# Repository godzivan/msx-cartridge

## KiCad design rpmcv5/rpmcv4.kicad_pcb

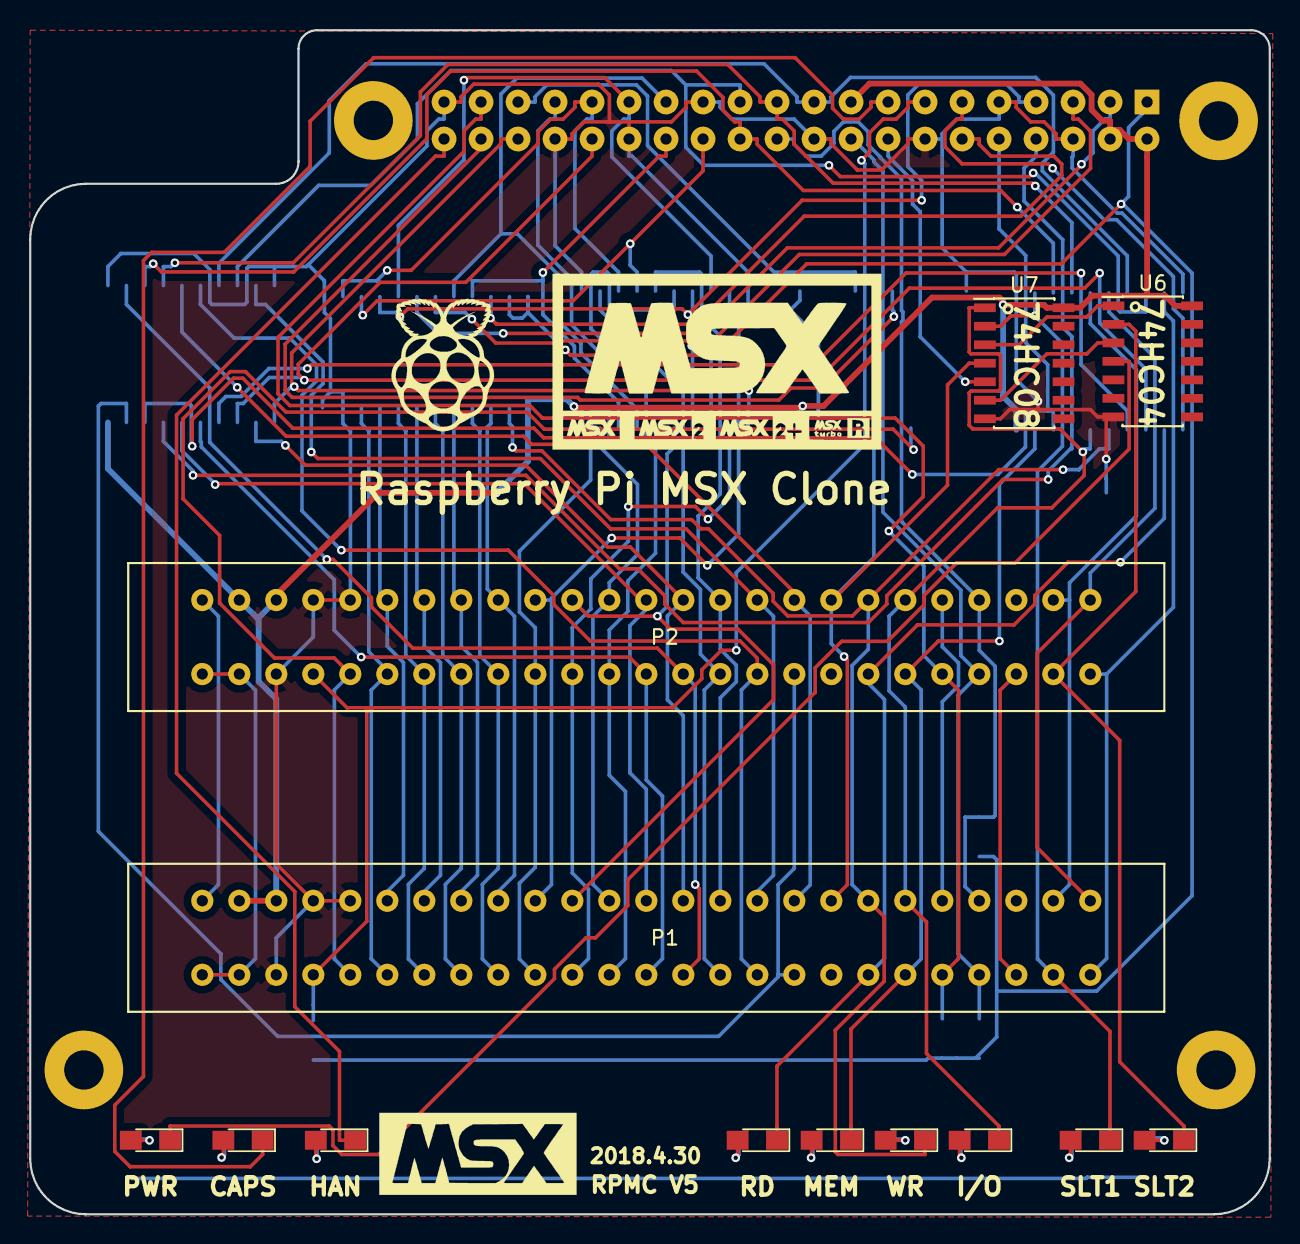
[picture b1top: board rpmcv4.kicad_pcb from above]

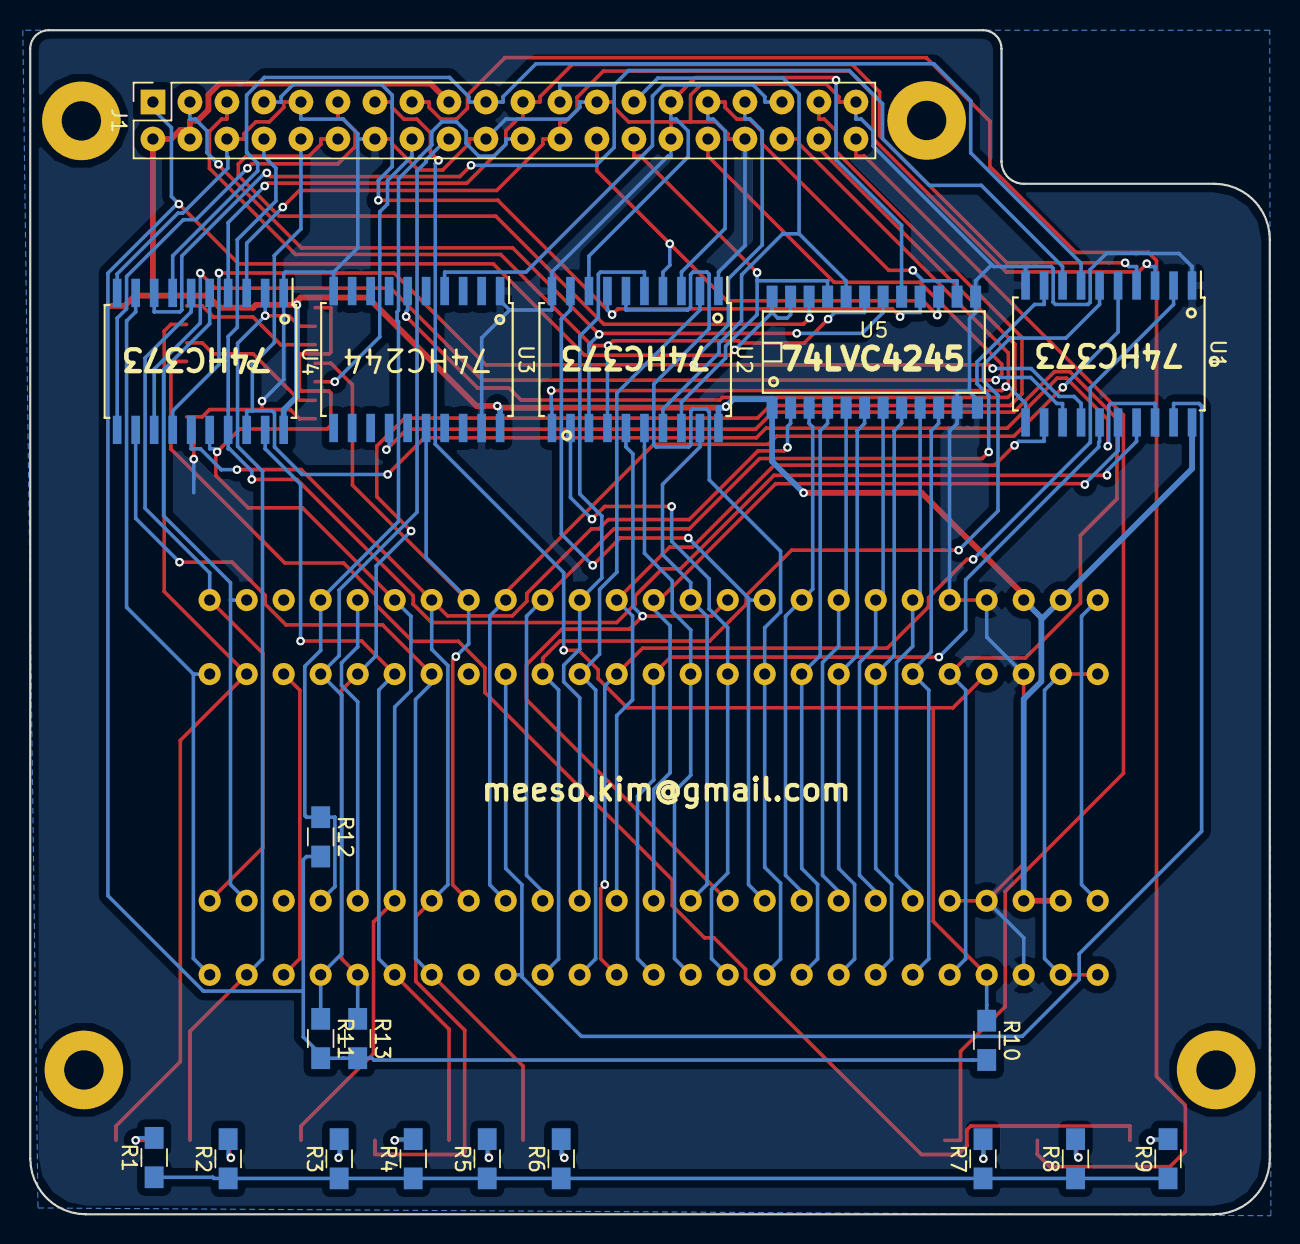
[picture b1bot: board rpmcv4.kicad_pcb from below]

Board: 2 copper layers, 85.1 x 81.3 mm, 38 parts (19 on the bottom side), 83 nets.

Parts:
D1, D2, D3, D4, D5, D6, D7, D8, D9: Led_Small; LED_0805_HandSoldering
G1: LOGO; raspberry_pi_logo
G2: LOGO; msx_msx2_msx+logo
J1: RPi_GPIO; Socket_Strip_Straight_2x20_Pitch2.54mm
P1, P2: CONN_02X25; MSX_SLOT
R1, R2, R3, R4, R5, R6, R7, R8, R9, R10, R11, R12, R13: R; R_0805_HandSoldering
REF1, REF2, REF3, REF4: MountingHole_2.7mm_Pad
U1, U2, U4: 74LS373; SOIC-20W_7.5x12.8mm_Pitch1.27mm
U3: 74HC244; SOIC-20W_7.5x12.8mm_Pitch1.27mm
U5: LVC4245; SOIC-24
U6: 74HC04; SOIC-14_3.9x8.7mm_Pitch1.27mm
U7: 74LS08; SOIC-14_3.9x8.7mm_Pitch1.27mm

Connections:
+3V3: J1.1, R10.2, R11.2, R12.2, R13.2, U5.23, U5.24
+5V: J1.2, J1.4, J1.17, P1.45, P1.47, P2.45, P2.47, U1.20, U2.20, U3.20, U4.20, U5.1, U6.14, U7.14
/+12V: P1.48, P1.50, P2.48, P2.50
/A0: P1.28, P2.28, U2.16
/A1: P1.27, P2.27, U2.19
/A2: P1.30, P2.30, U2.12
/A3: P1.29, P2.29, U2.15
/A4: P1.32, P2.32, U2.6
/A5: P1.31, P2.31, U2.9
/A6: P1.22, P2.22, U2.2
/A7: P1.21, P2.21, U2.5
/A8: P1.24, P2.24, U1.2
/A9: P1.17, P2.17, U1.5
/A10: P1.20, P2.20, U1.6
/A11: P1.19, P2.19, U1.9
/A12: P1.23, P2.23, U1.12
/A13: P1.26, P2.26, U1.15
/A14: P1.25, P2.25, U1.16
/A15: P1.18, P2.18, U1.19
/BUSDIR: J1.37, P1.10, P2.10, R13.1
/CAPS: D8.1, J1.15
/CLK: P1.42, P2.42, U3.14
/CS1: P1.1, P2.1, U4.6
/CS2: P1.2, P2.2, U4.9
/CS12: P1.3, P2.3, U4.5
/D0: P1.34, P2.34, U5.4
/D1: P1.33, P2.33, U5.3
/D2: P1.36, P2.36, U5.6
/D3: P1.35, P2.35, U5.5
/D4: P1.38, P2.38, U5.8
/D5: P1.37, P2.37, U5.7
/D6: P1.40, P2.40, U5.10
/D7: P1.39, P2.39, U5.9
/HAN: D7.1, J1.40
/INT: J1.18, P1.8, P2.8, R11.1
/IORQ: D3.1, P1.11, P2.11, U4.16, U7.1
/M1: P1.9, P2.9
/MREQ: D5.1, P1.12, P2.12, U4.19
/PWR: D9.1, U6.4
/RA8: J1.24, U1.3, U4.3
/RA9: J1.21, U1.4, U4.4
/RA10: J1.19, U1.7, U4.7
/RA11: J1.23, U1.8, U4.8
/RA12: J1.32, U1.13, U4.13
/RA13: J1.33, U1.14, U4.14
/RA14: J1.8, U1.17, U4.17
/RA15: J1.10, U1.18, U4.18
/RC16: J1.36, U1.11, U2.11
/RC17: J1.11, U4.11
/RC18: J1.12, U5.22
/RC19: J1.35, U3.4
/RC20: J1.38, U3.6
/RC23: J1.16, U7.5
/RC25: J1.22, P1.7, P2.7, R12.1
/RC27: J1.13, P1.44, P2.44, R10.1
/RD: D6.1, P1.14, P2.14, U4.12
/RD0: J1.27, U2.17, U5.20
/RD1: J1.28, U2.18, U5.21
/RD2: J1.3, U2.13, U5.18
/RD3: J1.5, U2.14, U5.19
/RD4: J1.7, U2.7, U5.16
/RD5: J1.29, U2.8, U5.17
/RD6: J1.31, U2.3, U5.14
/RD7: J1.26, U2.4, U5.15
/RESET: P1.15, P2.15, U3.16, U7.4
/RFSH: P1.6, P2.6
/SLTSL1: D2.1, P1.4, U4.2, U7.2
/SLTSL3: D1.1, P2.4, U6.2
/SNDIN: P1.49, P2.49
/V3.3: R1.1, R2.1, R3.1, R4.1, R5.1, R6.1, R7.1, R8.1, R9.1
/WR: D4.1, P1.13, P2.13, U4.15, U5.2
/nPWR: U6.3, U7.6
/nSLTSL3: U6.1, U7.3
GND: J1.6, J1.9, J1.14, J1.20, J1.25, J1.30, J1.34, J1.39, P1.41, P1.43, P1.46, P2.41, P2.43, P2.46, U1.1, U1.10, U2.1, U2.10, U3.1, U3.10, U3.19, U4.1, U4.10, U5.11, U5.12, U5.13, U6.7, U7.7
unnamed: D1.2, R1.2
unnamed: D2.2, R2.2
unnamed: D3.2, R3.2
unnamed: D4.2, R4.2
unnamed: D5.2, R5.2
unnamed: D6.2, R6.2
unnamed: D7.2, R7.2
unnamed: D8.2, R8.2
unnamed: D9.2, R9.2

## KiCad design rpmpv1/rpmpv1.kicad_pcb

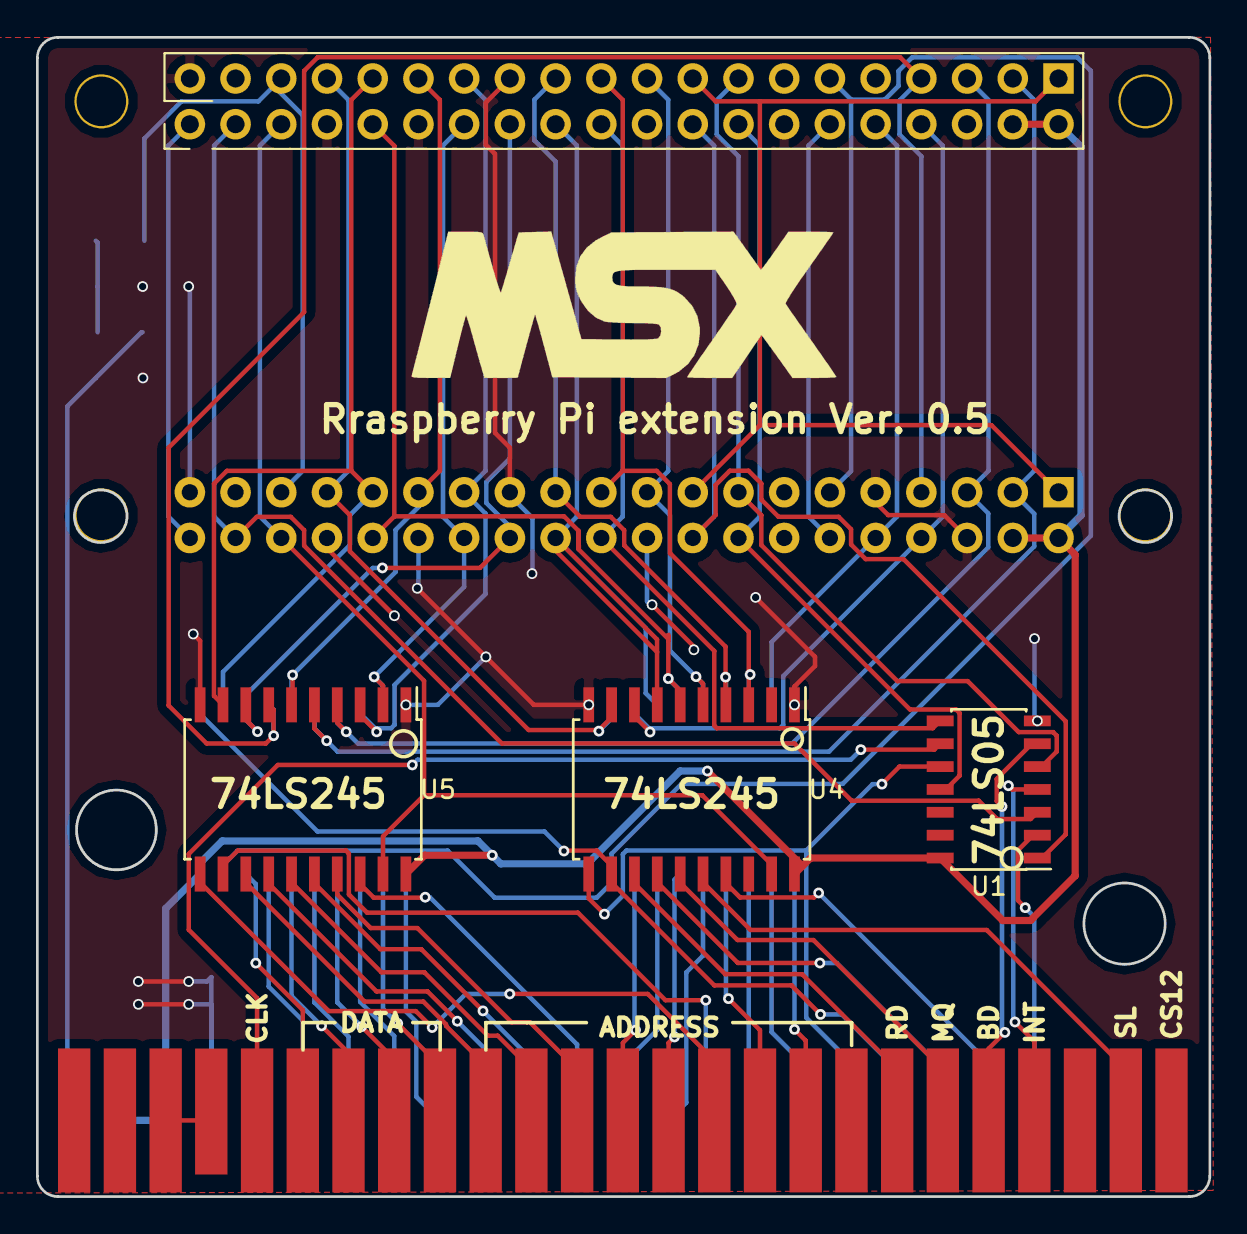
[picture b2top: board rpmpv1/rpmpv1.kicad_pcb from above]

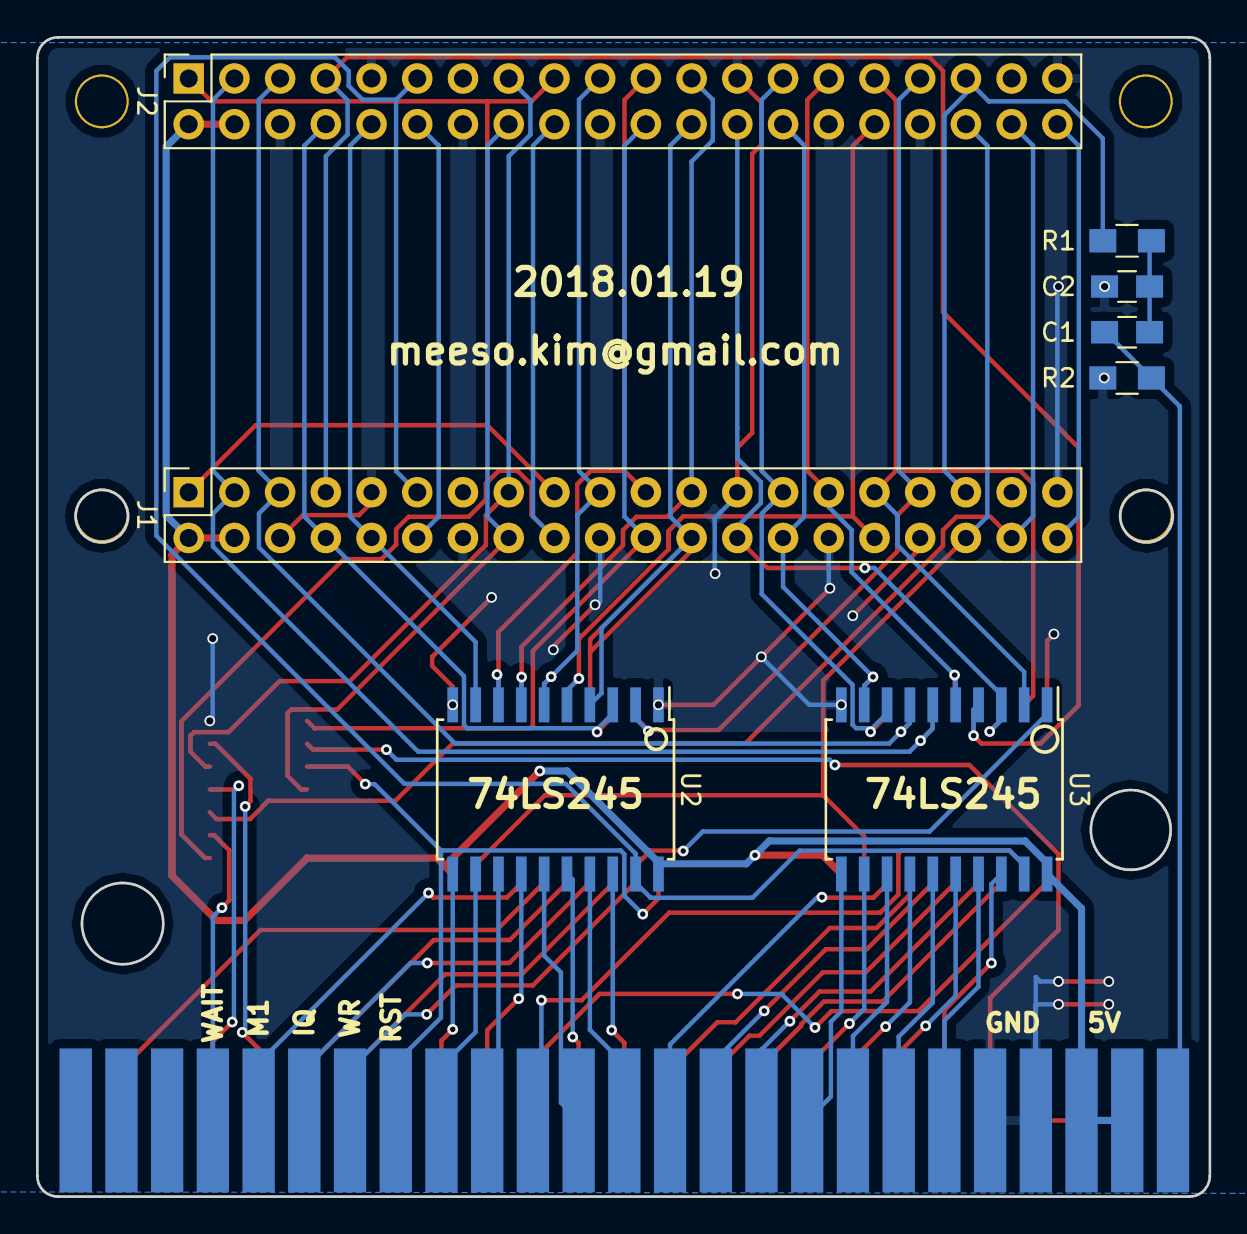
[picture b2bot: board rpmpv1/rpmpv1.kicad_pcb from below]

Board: 2 copper layers, 65.1 x 64.4 mm, 11 parts (8 on the bottom side), 33 nets.

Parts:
C1: 33n; C_0805_HandSoldering
C2: 10u; C_0805_HandSoldering
J1, J2: RPi_GPIO; Socket_Strip_Straight_2x20_Pitch2.54mm
R1: 270R; R_0805_HandSoldering
R2: 150R; R_0805_HandSoldering
U1: 74LS05; SOIC-14_3.9x8.7mm_Pitch1.27mm
U2, U3, U4, U5: 74LS245; SOIC-20W_7.5x12.8mm_Pitch1.27mm

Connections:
+3V3: J1.1, J1.17, J2.1, J2.17
+5V: J1.2, J1.4, J2.2, J2.4, U1.14, U2.20, U3.20, U4.20, U5.20
/BCK: J1.12, J2.12
/DOUT: J1.40, J2.40
/LE_A: J1.36, J2.36, U4.19, U5.19
/LE_B: J1.11, J2.11, U2.19, U3.19
/LRCK: J1.35, J2.35, R1.2
/RA8: J1.24, J2.24, U2.4, U4.7
/RA9: J1.21, J2.21, U2.8, U4.3
/RA10: J1.19, J2.19, U2.6, U4.5
/RA11: J1.23, J2.23, U2.7, U4.4
/RA12: J1.32, J2.32, U2.5, U4.6
/RA13: J1.33, J2.33, U2.2, U4.9
/RA14: J1.8, J2.8, U2.3, U4.8
/RA15: J1.10, J2.10, U2.9
/RBUSDIR: J1.15, J2.15, U1.5
/RCLK: J1.22, J2.22, U1.8
/RD0: J1.27, J2.27, U3.8, U5.3
/RD1: J1.28, J2.28, U3.9, U5.2
/RD2: J1.3, J2.3, U3.6, U5.5
/RD3: J1.5, J2.5, U3.7, U5.4
/RD4: J1.7, J2.7, U3.4, U5.7
/RD5: J1.29, J2.29, U3.5, U5.6
/RD6: J1.31, J2.31, U3.2, U5.9
/RD7: J1.26, J2.26, U3.3, U5.8
/RESET: U1.10, U4.11
/RINT: J1.38, J2.38, U1.3
/RRESET: J1.16, J2.16, U1.11
/RWAIT: J1.18, J2.18, U1.1
/SOUNDIN: C2.1, R2.1
/WR: U3.1, U4.12
GND: C1.2, J1.6, J1.9, J1.14, J1.20, J1.25, J1.30, J1.34, J1.39, J2.6, J2.9, J2.14, J2.20, J2.25, J2.30, J2.34, J2.39, R2.2, U1.7, U2.1, U2.10, U3.10, U4.1, U4.10, U5.1, U5.10
unnamed: C1.1, C2.2, R1.1

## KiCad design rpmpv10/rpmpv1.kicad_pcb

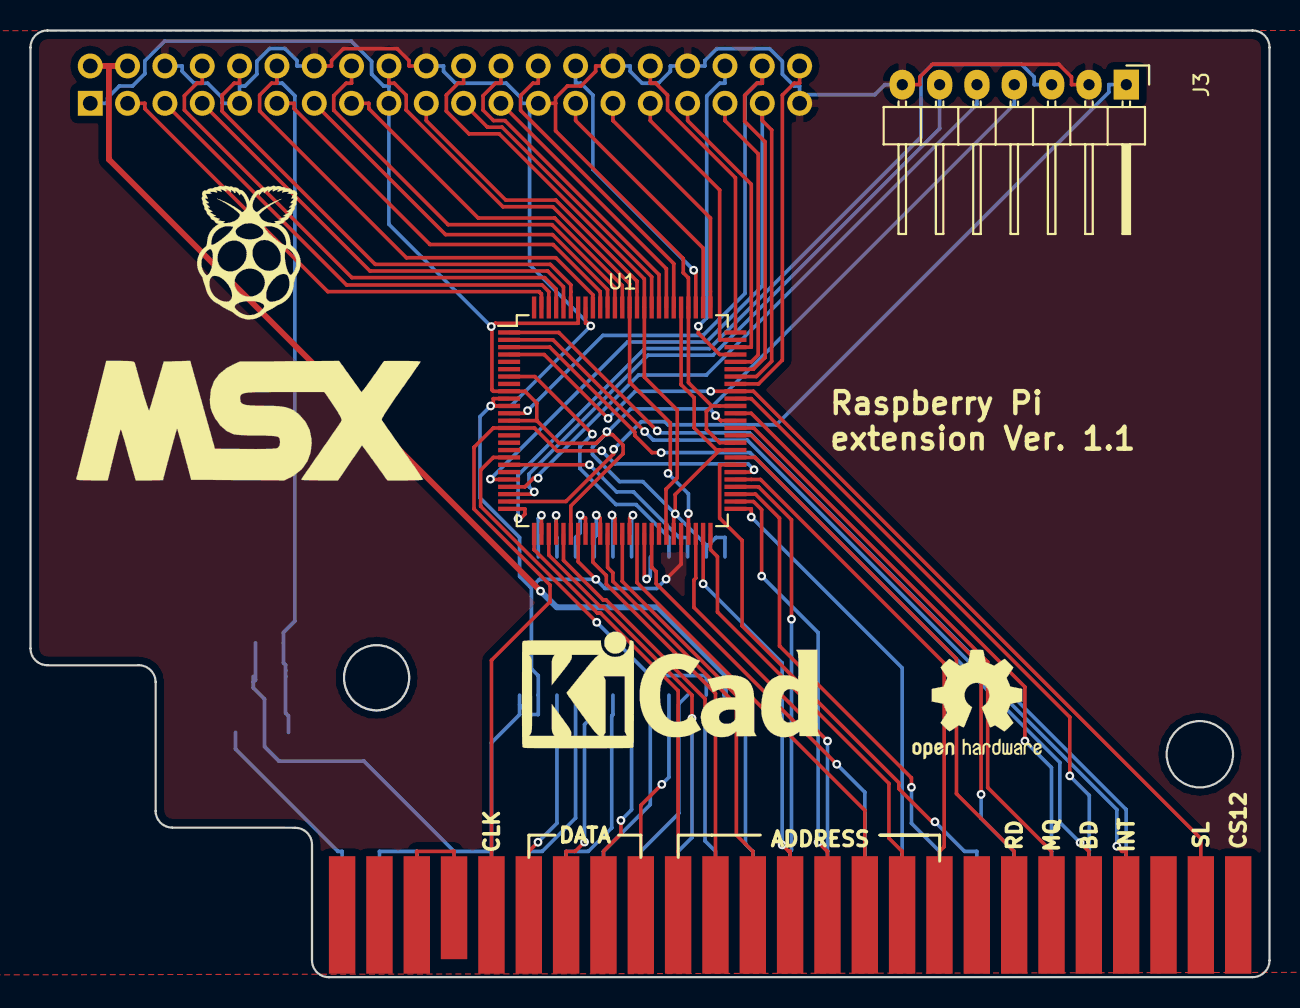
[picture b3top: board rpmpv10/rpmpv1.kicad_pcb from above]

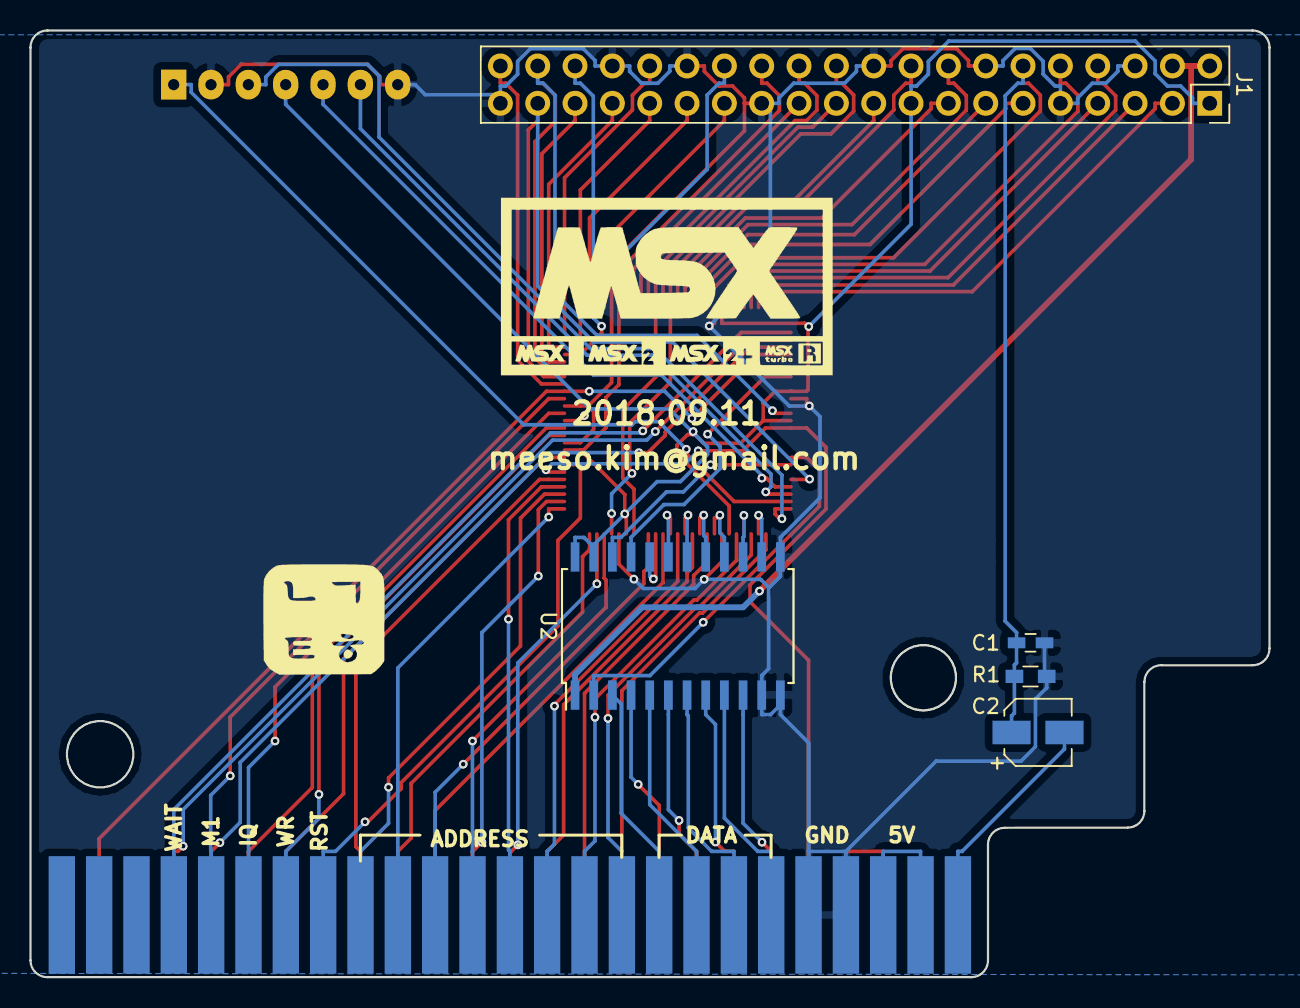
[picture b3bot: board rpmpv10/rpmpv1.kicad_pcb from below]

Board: 2 copper layers, 84.3 x 64.4 mm, 14 parts (7 on the bottom side), 83 nets.

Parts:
C1: C; C_0603_HandSoldering
C2: CP; CP_Elec_4x5.3
G1: LOGO; raspberry_pi_logo
G2: LOGO; msx_msx2_msx+logo
G3: LOGO; msx-logo
G5: LOGO3; srxg
J1: RPi_GPIO; Socket_Strip_Straight_2x20_Pitch2.54mm
J3: Conn_01x07; Pin_Header_Angled_1x07
P1: CONN_02X25; card_edge_connector
R1: R; R_0603_HandSoldering
REF1: OSHW-Logo2_9.8x8mm_SilkScreen
REF2: KiCad-Logo_8mm_SilkScreen
U1: MaxII_EPM240; TQFP-100_14x14mm_Pitch0.5mm
U2: LVC4245; SOIC-24W_7.5x15.4mm_Pitch1.27mm

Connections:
+3V3: J1.1, J1.17, J3.4, U1.9, U1.13, U1.31, U1.45, U1.59, U1.63, U1.80, U1.94, U2.23, U2.24
+5V: J1.2, J1.4, U2.1
/A0: P1.28, U1.36
/A1: P1.27, U1.38
/A2: P1.30, U1.34
/A3: P1.29, U1.30
/A4: P1.32, U1.26
/A5: P1.31, U1.28
/A6: P1.22, U1.40
/A7: P1.21, U1.42
/A8: P1.24, U1.52
/A9: P1.17, U1.53
/A10: P1.20, U1.50
/A11: P1.19, U1.51
/A12: P1.23, U1.48
/A13: P1.26, U1.49
/A14: P1.25, U1.54
/A15: P1.18, U1.55
/BUSDIR: P1.10, U1.3
/CLK: P1.42, U1.14, U1.56
/D0: P1.34, U2.4
/D1: P1.33, U2.3
/D2: P1.36, U2.6
/D03: U1.41, U2.20
/D3: P1.35, U2.5
/D4: P1.38, U2.8
/D5: P1.37, U2.7
/D6: P1.40, U2.10
/D7: P1.39, U2.9
/D13: U1.7, U2.21
/D23: U1.37, U2.18
/D33: U1.39, U2.19
/D43: U1.33, U2.16
/D53: U1.35, U2.17
/D63: U1.27, U2.14
/D73: U1.29, U2.15
/DAT_CE: U1.19, U2.22
/DAT_DIR: U1.18, U2.2
/INT: P1.8, U1.2
/IORQ: P1.11, U1.64
/M1: P1.9, U1.66
/MREQ: P1.12, U1.62
/RA8: J1.24, U1.83
/RA9: J1.21, U1.84
/RA10: J1.19, U1.86
/RA11: J1.23, U1.82
/RA12: J1.32, U1.75
/RA13: J1.33, U1.73
/RA14: J1.8, U1.97
/RA15: J1.10, U1.95
/RC16: J1.36, U1.72
/RC17: J1.11, U1.91
/RC18: C1.1, C2.1, J1.12, R1.1, U1.92
/RC19: J1.35, U1.71
/RC20: J1.38, U1.12, U1.70
/RC21: J1.40, U1.68
/RC22: J1.15, U1.88
/RC23: J1.16, U1.89
/RC24: J1.18, U1.47, U1.87
/RC25: J1.22, U1.44, U1.85
/RC26: J1.37, U1.21, U1.69
/RC27: J1.13, U1.90
/RD: P1.14, U1.58
/RD0: J1.27, U1.77
/RD1: J1.28, U1.78
/RD2: J1.3, U1.99
/RD3: J1.5, U1.98
/RD4: J1.7, U1.96
/RD5: J1.29, U1.76
/RD6: J1.31, U1.74
/RD7: J1.26, U1.81
/RESET: P1.15, U1.57
/SLTSL: P1.4, U1.4, U1.67
/SOUNDIN: C2.2, P1.49
/TCK: J3.1, U1.24
/TDI: J3.6, U1.23
/TDO: J3.3, U1.25
/TMS: J3.5, U1.22
/VCC: P1.45, P1.47
/WAIT: P1.7, U1.1
/WR: P1.13, U1.61
GND: C1.2, J1.6, J1.9, J1.14, J1.20, J1.25, J1.30, J1.34, J1.39, J3.2, J3.7, P1.41, P1.43, R1.2, U1.10, U1.11, U1.32, U1.46, U1.60, U1.65, U1.79, U1.93, U2.11, U2.12, U2.13
unnamed: P1.44, P1.46

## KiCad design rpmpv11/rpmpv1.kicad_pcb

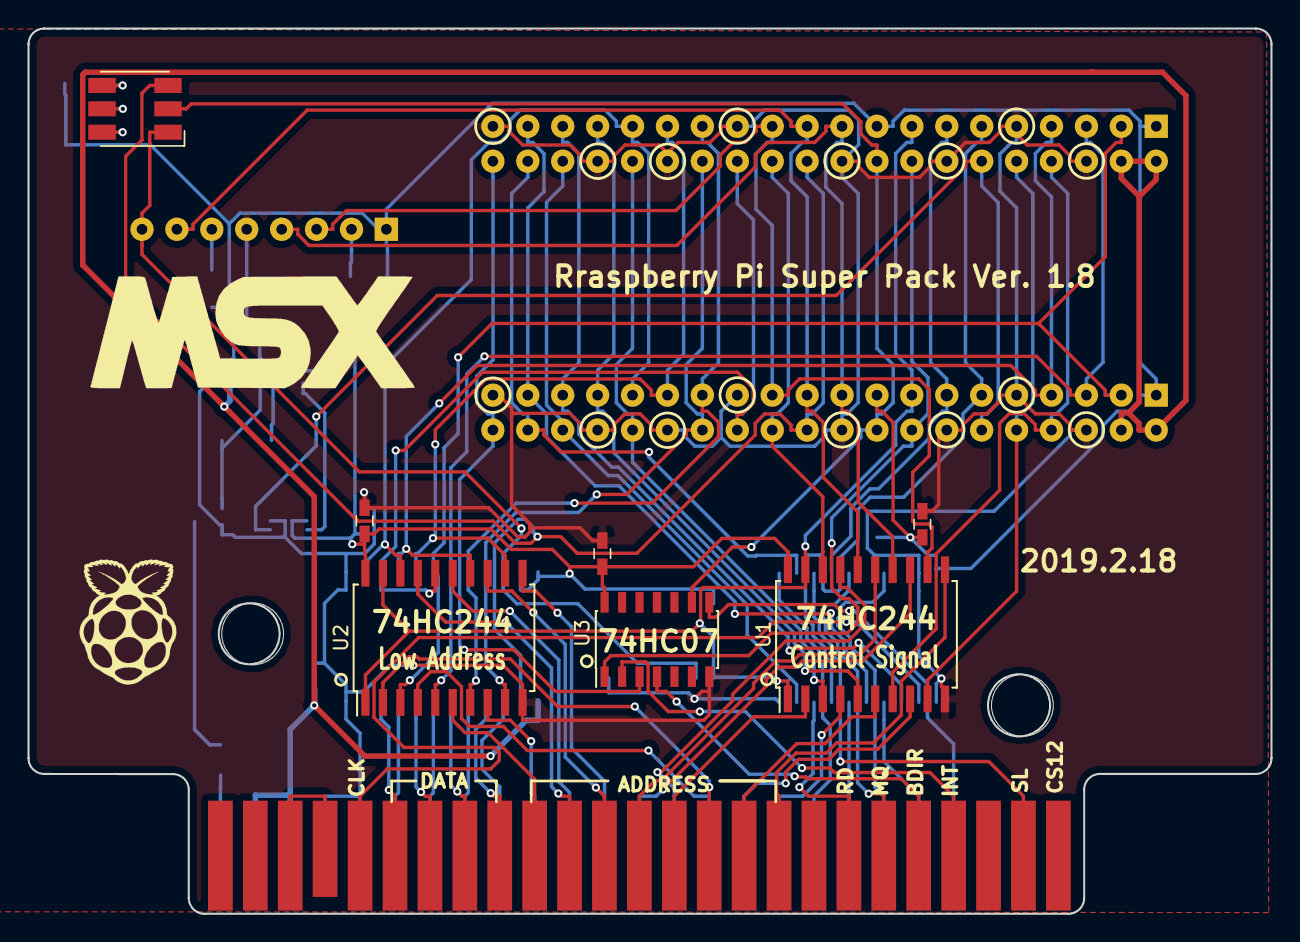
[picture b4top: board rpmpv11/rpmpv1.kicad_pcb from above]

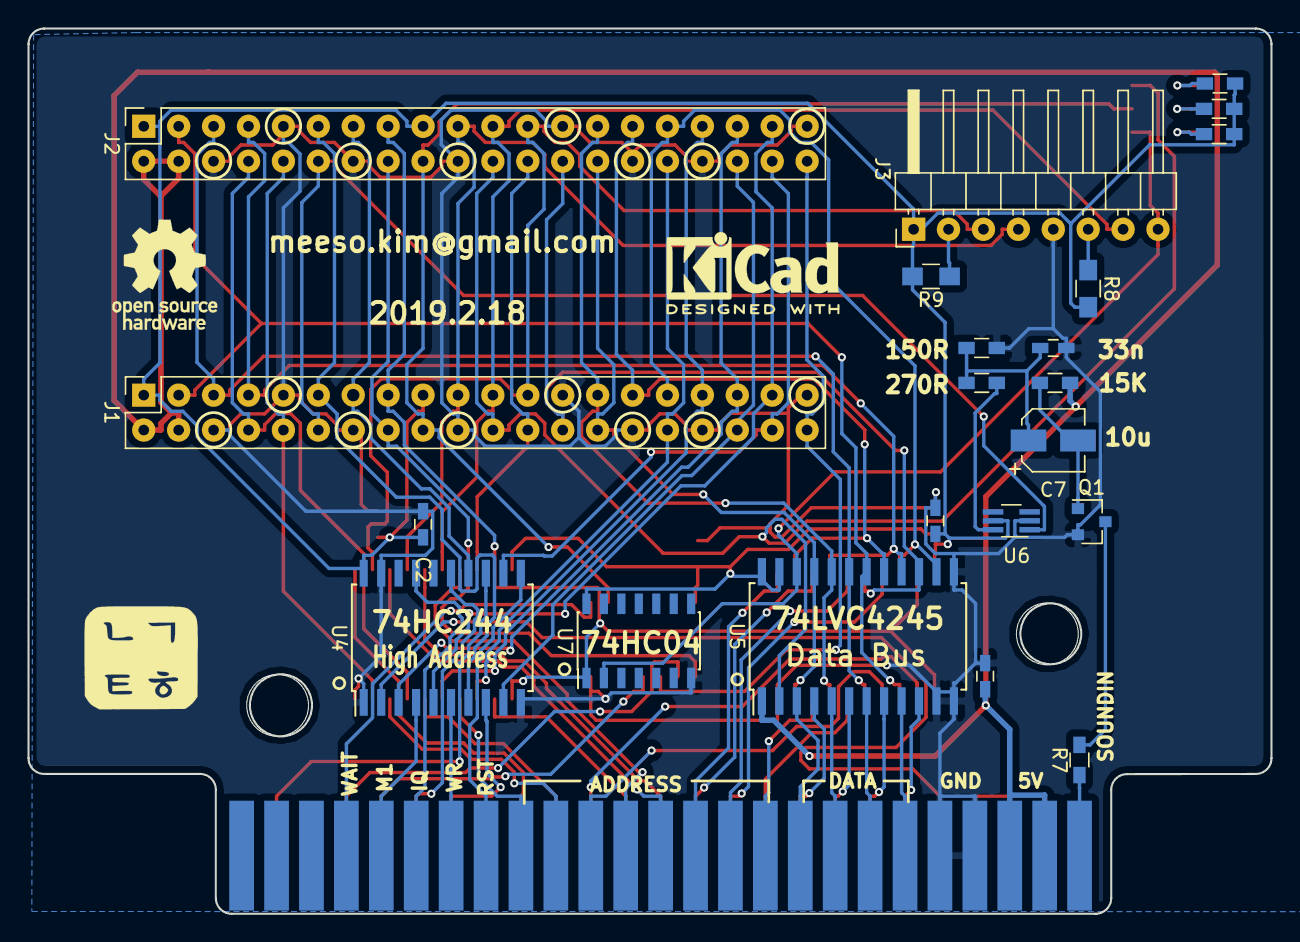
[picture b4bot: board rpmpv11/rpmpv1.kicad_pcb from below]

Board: 2 copper layers, 90.4 x 64.4 mm, 34 parts (24 on the bottom side), 78 nets.

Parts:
C1, C2, C3, C4, C5, C6, C8: C; C_0603_HandSoldering
C7: CP; CP_Elec_4x4.5
D1: LED_RGB; LED_RGB_5050-6
G1: LOGO; raspberry_pi_logo
G2: LOGO; msx-logo
J1, J2: RPi_GPIO; Socket_Strip_Straight_2x20_Pitch2.54mm
J3: Conn_01x08; Pin_Header_Angled_1x08_Pitch2.54mm
P1: CONN_02X25; card_edge_connector
Q1: Q_NPN_BEC; SOT-23
R1, R2, R3, R4, R5, R6, R7: R; R_0603_HandSoldering
R8, R9: R; R_0805_HandSoldering
REF2: OSHW-Logo_7.5x8mm_SilkScreen
REF3: KiCad-Logo2_6mm_SilkScreen
U1, U2, U4: 74HC244; SOIC-20W_7.5x12.8mm_Pitch1.27mm
U3: 74LS07; SOIC-14_3.9x8.7mm_Pitch1.27mm
U5: LVC4245; SOIC-24W_7.5x15.4mm_Pitch1.27mm
U6: NC7WZ16; SOT-363_SC-70-6_Handsoldering
U7: 74HC04; SOIC-14_3.9x8.7mm_Pitch1.27mm

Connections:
+3V3: C1.1, C2.1, C3.1, C4.1, C5.1, J1.1, J1.17, J2.1, J2.17, J3.1, R1.2, R2.2, R3.2, R8.2, R9.2, U1.20, U2.20, U3.14, U4.20, U5.23, U5.24, U6.5, U7.14
+5V: C8.2, J1.2, J1.4, J2.2, J2.4, P1.45, P1.47, R6.1, U5.1
/A0: P1.28, U2.13
/A1: P1.27, U2.11
/A2: P1.30, U2.17
/A3: P1.29, U2.15
/A4: P1.32, U2.6
/A5: P1.31, U2.8
/A6: P1.22, U2.2
/A7: P1.21, U2.4
/A8: P1.24, U1.2
/A9: P1.17, U1.4
/A10: P1.20, U1.6
/A11: P1.19, U1.8
/A12: P1.23, U1.17
/A13: P1.26, U1.15
/A14: P1.25, U1.13
/A15: P1.18, U1.11
/ADDR: J1.15, J2.15, U1.1, U1.19, U2.1, U2.19, U7.1
/BUSDIR: P1.10, U3.4
/CLK: P1.42, U4.2
/CS: D1.1, J3.8, U5.22, U7.2
/D0: P1.34, U5.4
/D1: P1.33, U5.3
/D2: P1.36, U5.6
/D3: P1.35, U5.5
/D4: P1.38, U5.8
/D5: P1.37, U5.7
/D6: P1.40, U5.10
/D7: P1.39, U5.9
/DAT_DIR: D1.3, J1.22, J2.22, U5.2
/INT: P1.8, U3.2
/IORQ: P1.11, U4.17
/M1: P1.9, U4.4
/MISO: J1.21, J2.21, J3.7, U1.16
/MOSI: J1.19, J2.19, J3.4, U1.14
/MREQ: P1.12, U4.15
/RA8: J1.24, J2.24, U1.18
/RA11: J1.23, J2.23, J3.3, U1.12
/RA12: J1.32, J2.32, U1.3
/RA13: J1.33, J2.33, U1.5
/RA14: J1.8, J2.8, U1.7
/RA15: J1.10, J2.10, U1.9
/RC16: J1.36, J2.36, U4.9
/RC17: J1.11, J2.11, U4.7
/RC18: J1.12, J2.12, U6.1
/RC19: J1.35, J2.35, U4.3
/RC20: J1.38, J2.38, U4.12
/RC21: J1.40, J2.40, U3.3
/RC23: J1.16, J2.16, U3.1
/RC24: D1.2, J1.18, J2.18, U3.9
/RC26: J1.37, J2.37, U4.5
/RC27: J1.13, J2.13, U4.14
/RD: P1.14, U4.8
/RD0: J1.27, J2.27, U2.7, U5.20
/RD1: J1.28, J2.28, U2.9, U5.21
/RD2: J1.3, J2.3, U2.3, U5.18
/RD3: J1.5, J2.5, U2.5, U5.19
/RD4: J1.7, J2.7, U2.14, U5.16
/RD5: J1.29, J2.29, U2.12, U5.17
/RD6: J1.31, J2.31, U2.18, U5.14
/RD7: J1.26, J2.26, U2.16, U5.15
/RESET: P1.15, U4.11
/SLTSL: P1.4, U4.13
/SOUNDIN: P1.49, R7.1
/WAIT: P1.7, U3.8
/WR: P1.13, U4.6
GND: C1.2, C2.2, C3.2, C4.2, C5.2, C6.2, C8.1, J1.6, J1.9, J1.14, J1.20, J1.25, J1.30, J1.34, J1.39, J2.6, J2.9, J2.14, J2.20, J2.25, J2.30, J2.34, J2.39, J3.5, P1.41, P1.43, Q1.2, R5.2, U1.10, U2.10, U3.7, U4.1, U4.10, U4.19, U5.11, U5.12, U5.13, U6.2, U7.7
unnamed: C6.1, C7.1, R4.2, R5.1
unnamed: C7.2, Q1.1, R6.2
unnamed: D1.4, R3.1
unnamed: D1.5, R2.1
unnamed: D1.6, R1.1
unnamed: J3.2, R9.1
unnamed: J3.6, R8.1
unnamed: P1.44, P1.46
unnamed: Q1.3, R7.2
unnamed: R4.1, U6.6
